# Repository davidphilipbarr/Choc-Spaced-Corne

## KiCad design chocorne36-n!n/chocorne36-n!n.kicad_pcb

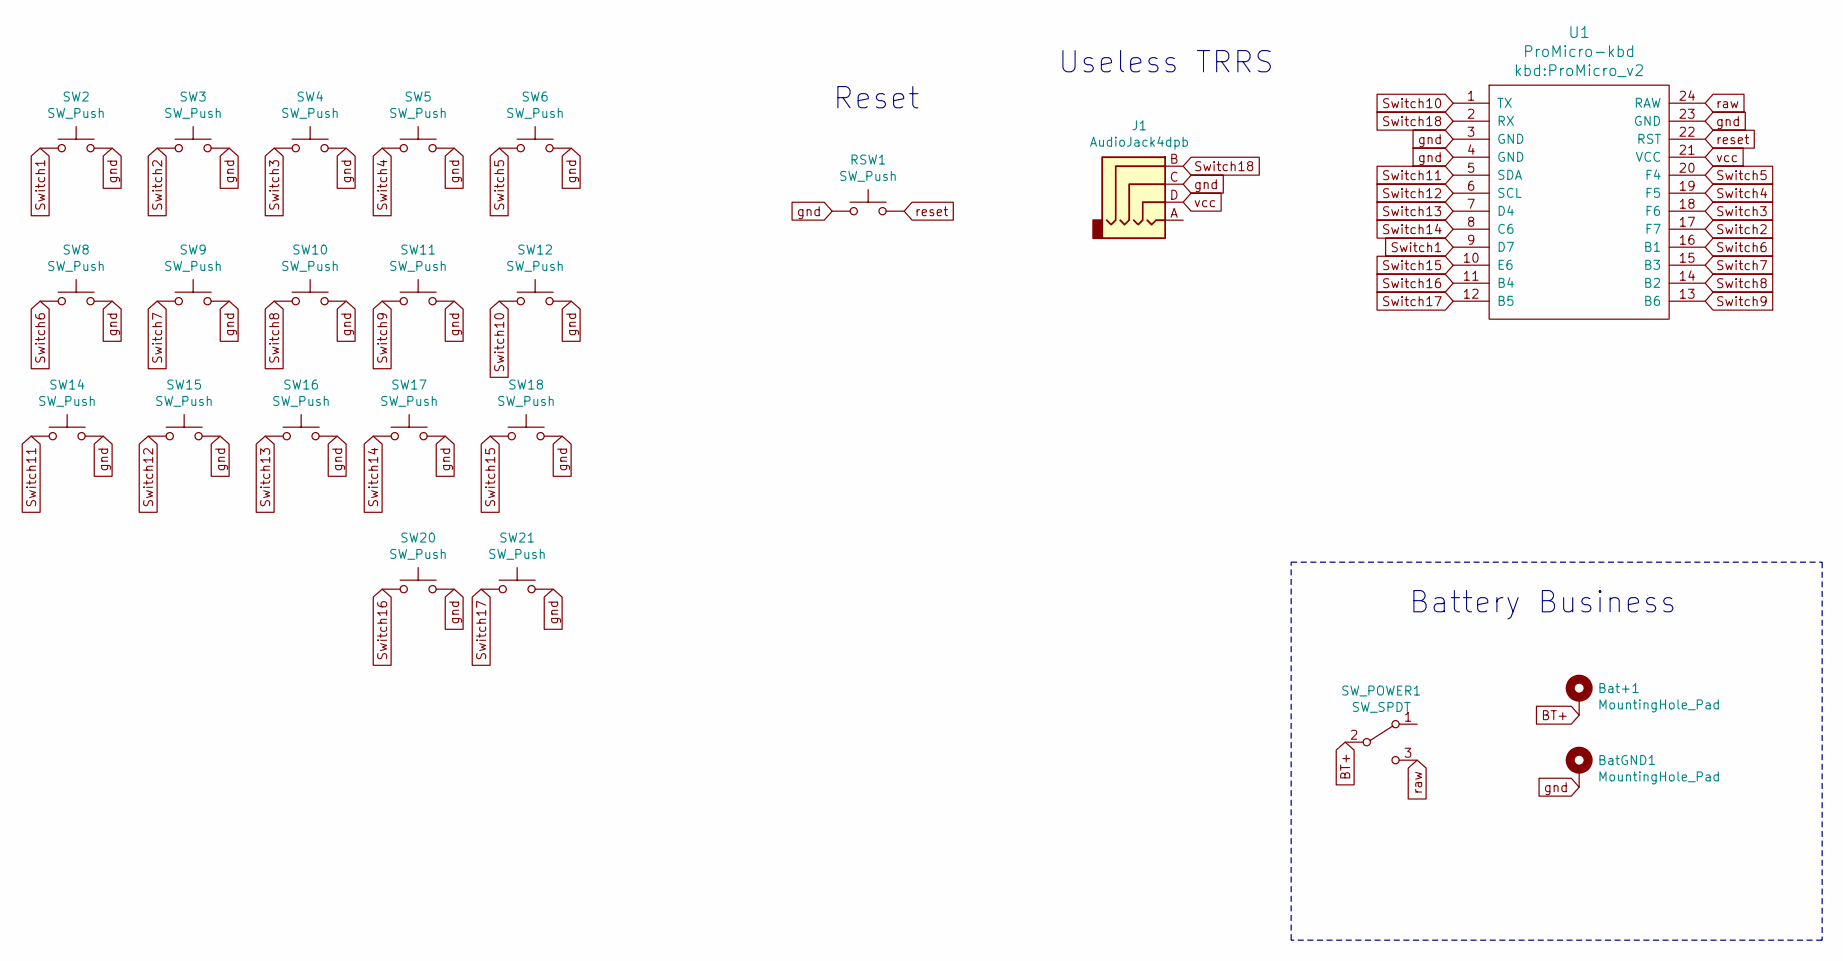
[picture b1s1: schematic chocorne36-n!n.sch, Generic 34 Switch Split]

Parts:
Bat+1: MountingHole_Pad; 1pin_conn
BatGND1: MountingHole_Pad; 1pin_conn
J1: AudioJack4dpb; MJ-4PP-9
RSW1: SW_Push; ResetSW
SW2, SW3, SW4, SW5, SW6, SW8, SW9, SW10, SW11, SW12, SW14, SW15, SW16, SW17, SW18, SW20, SW21: SW_Push; SW_PG1350_rev_DPB
SW_POWER1: SW_SPDT; SPDT_C128955
U1: ProMicro-kbd; ProMicro_v2

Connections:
BT+: Bat+1.1, SW_POWER1.2 (B)
Switch1: SW2.1, U1.9 (D7)
Switch2: SW3.1, U1.17 (F7)
Switch3: SW4.1, U1.18 (F6)
Switch4: SW5.1, U1.19 (F5)
Switch5: SW6.1, U1.20 (F4)
Switch6: SW8.1, U1.16 (B1)
Switch7: SW9.1, U1.15 (B3)
Switch8: SW10.1, U1.14 (B2)
Switch9: SW11.1, U1.13 (B6)
Switch10: SW12.1, U1.1 (TX)
Switch11: SW14.1, U1.5 (SDA)
Switch12: SW15.1, U1.6 (SCL)
Switch13: SW16.1, U1.7 (D4)
Switch14: SW17.1, U1.8 (C6)
Switch15: SW18.1, U1.10 (E6)
Switch16: SW20.1, U1.11 (B4)
Switch17: SW21.1, U1.12 (B5)
Switch18: J1.B, U1.2 (RX); also elsewhere on the board
gnd: BatGND1.1, J1.C, RSW1.1, SW2.2, SW3.2, SW4.2, SW5.2, SW6.2, SW8.2, SW9.2, SW10.2, SW11.2, SW12.2, SW14.2, SW15.2, SW16.2, SW17.2, SW18.2, SW20.2, SW21.2, U1.3 (GND), U1.4 (GND), U1.23 (GND); also elsewhere on the board
raw: SW_POWER1.3 (C), U1.24 (RAW)
reset: RSW1.2, U1.22 (RST)
vcc: J1.D, U1.21 (VCC)

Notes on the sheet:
Battery Business
Useless TRRS
Reset

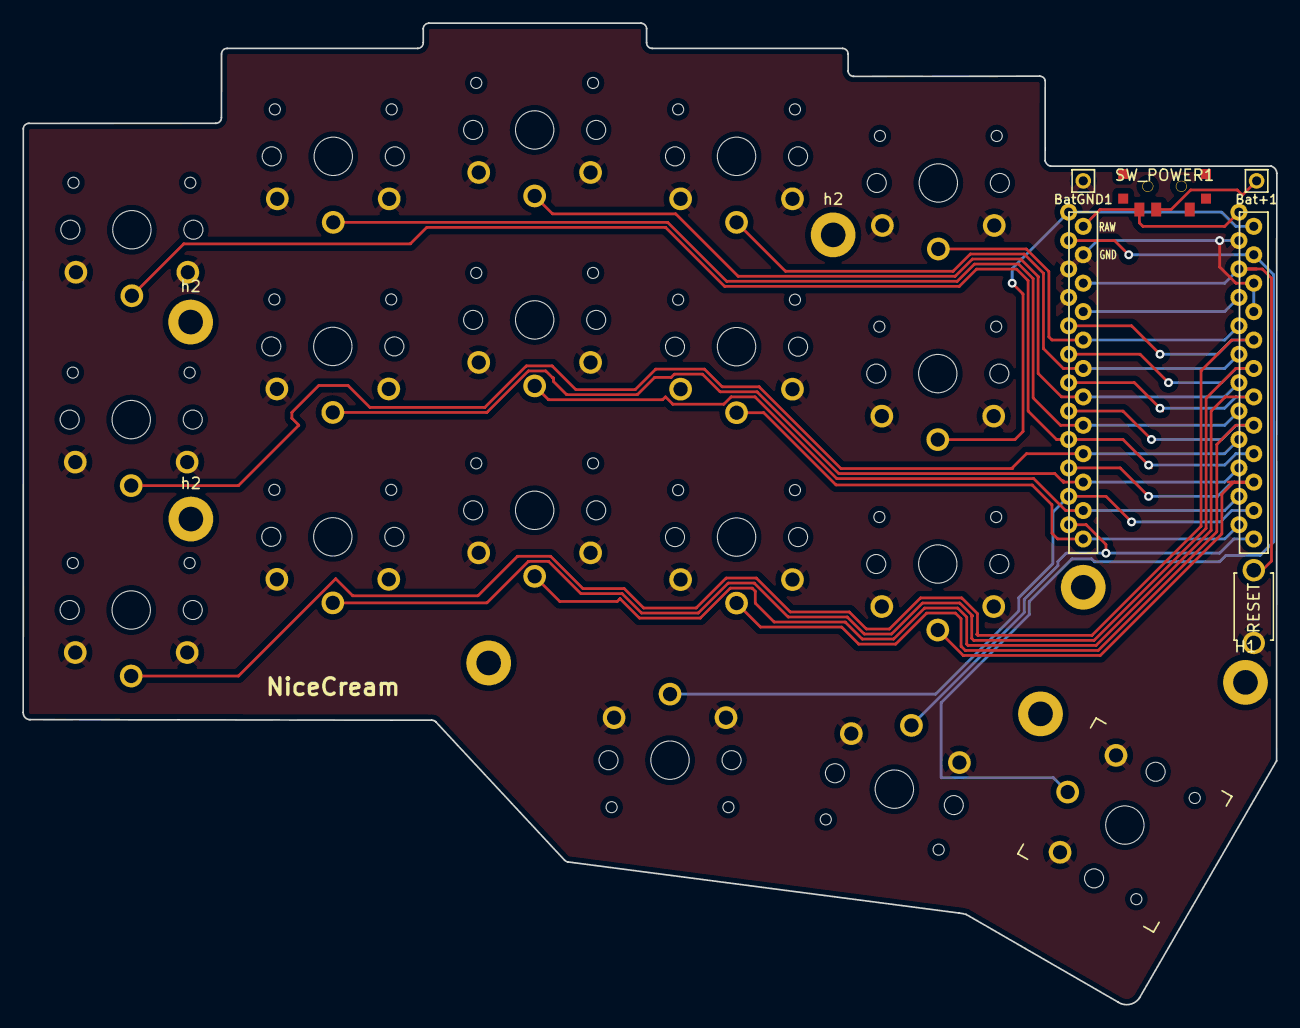
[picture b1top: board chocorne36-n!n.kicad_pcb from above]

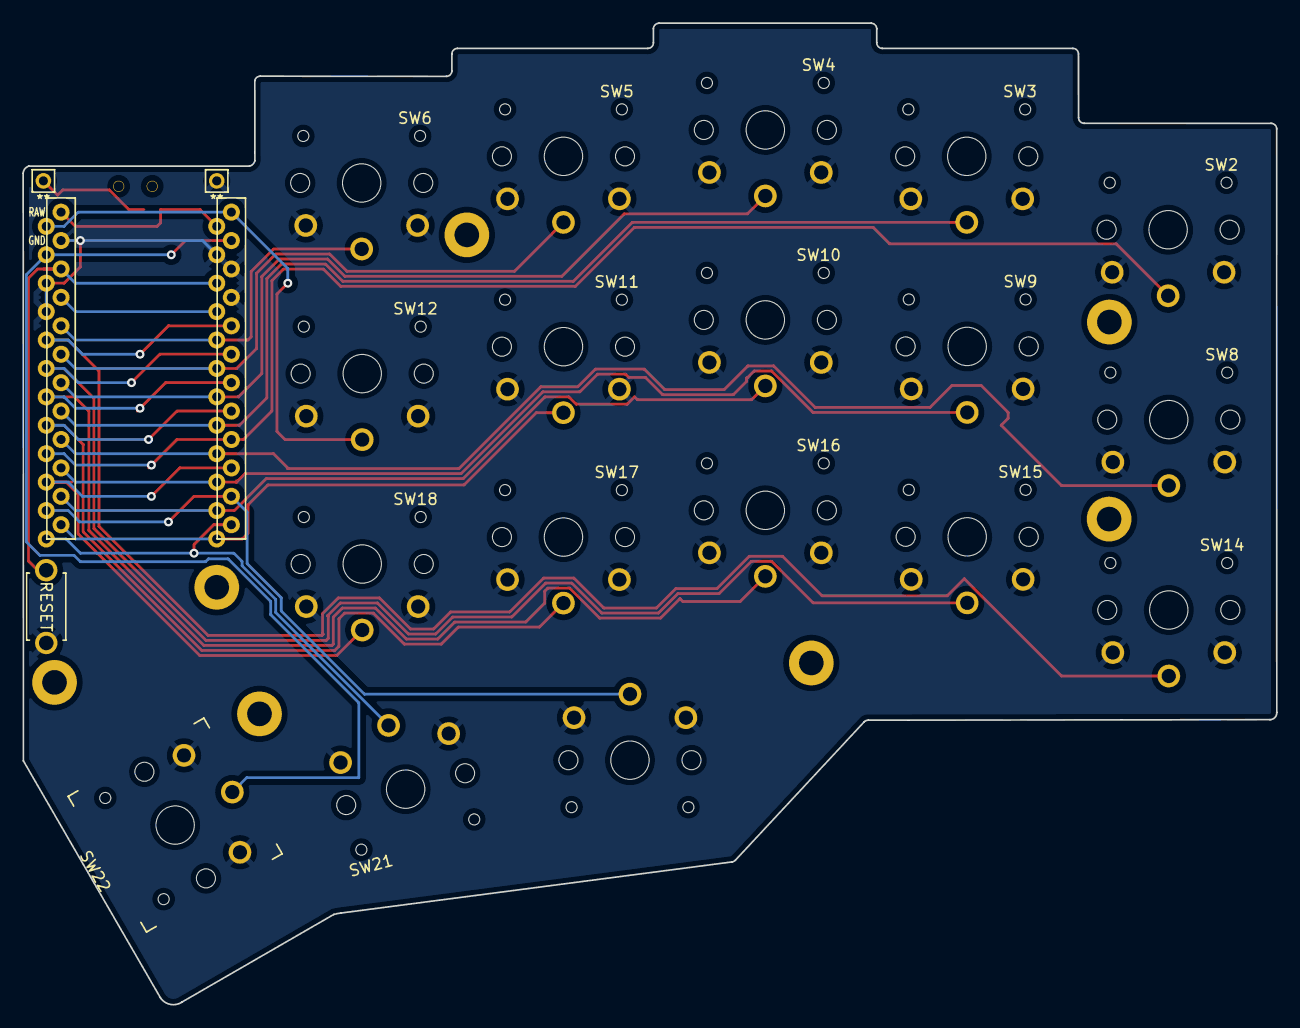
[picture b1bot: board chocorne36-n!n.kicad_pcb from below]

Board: 2 copper layers, 112.0 x 87.7 mm, 27 parts (2 on the bottom side), 22 nets.

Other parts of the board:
H1: h1; LEGO_HOLE
SW22: SW_Push; SW_PG1350_15_reversible_b2
h2, h2#2, h2#3: h2; LEGO_HOLE

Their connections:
Switch18: SW22.1; also elsewhere on the board
gnd: SW22.2; also elsewhere on the board

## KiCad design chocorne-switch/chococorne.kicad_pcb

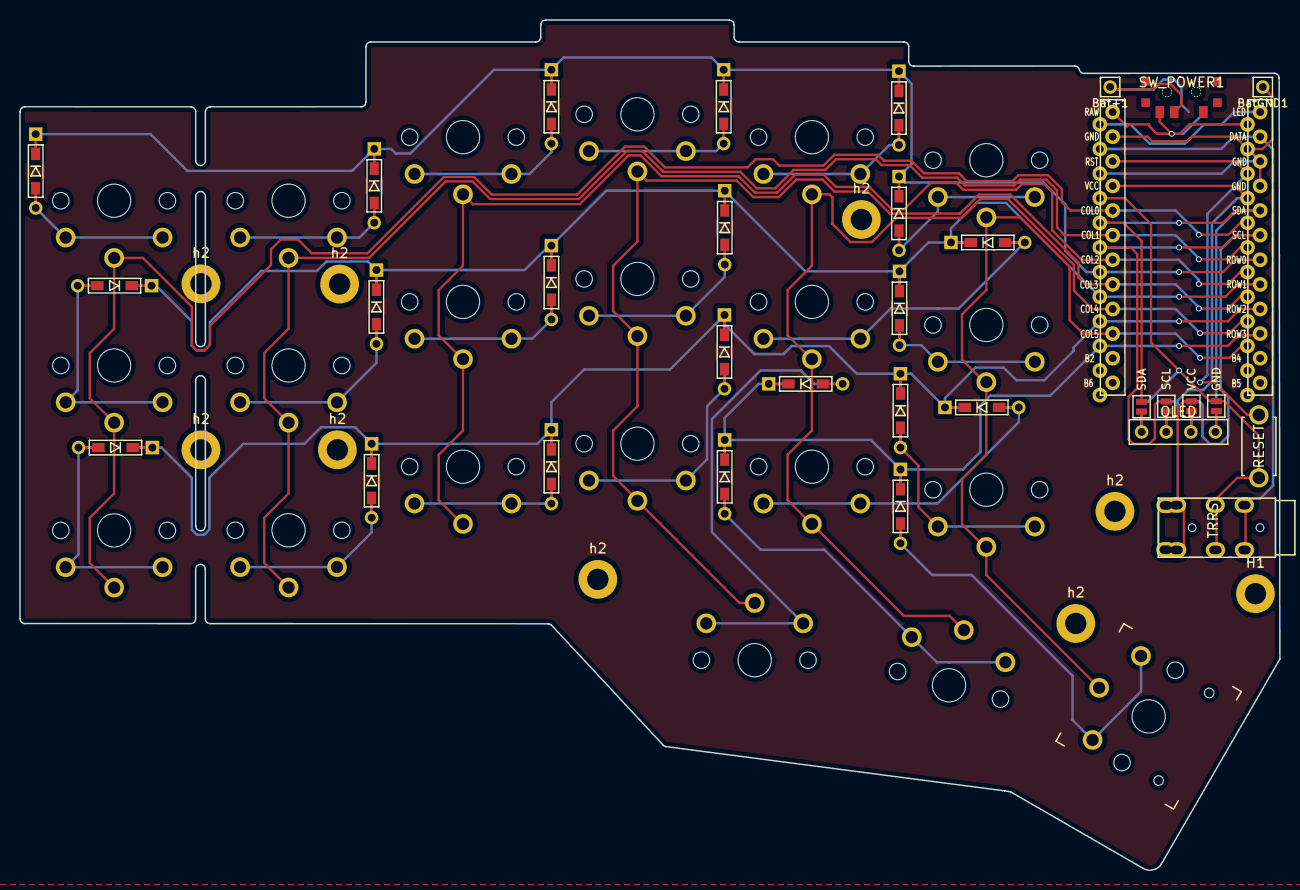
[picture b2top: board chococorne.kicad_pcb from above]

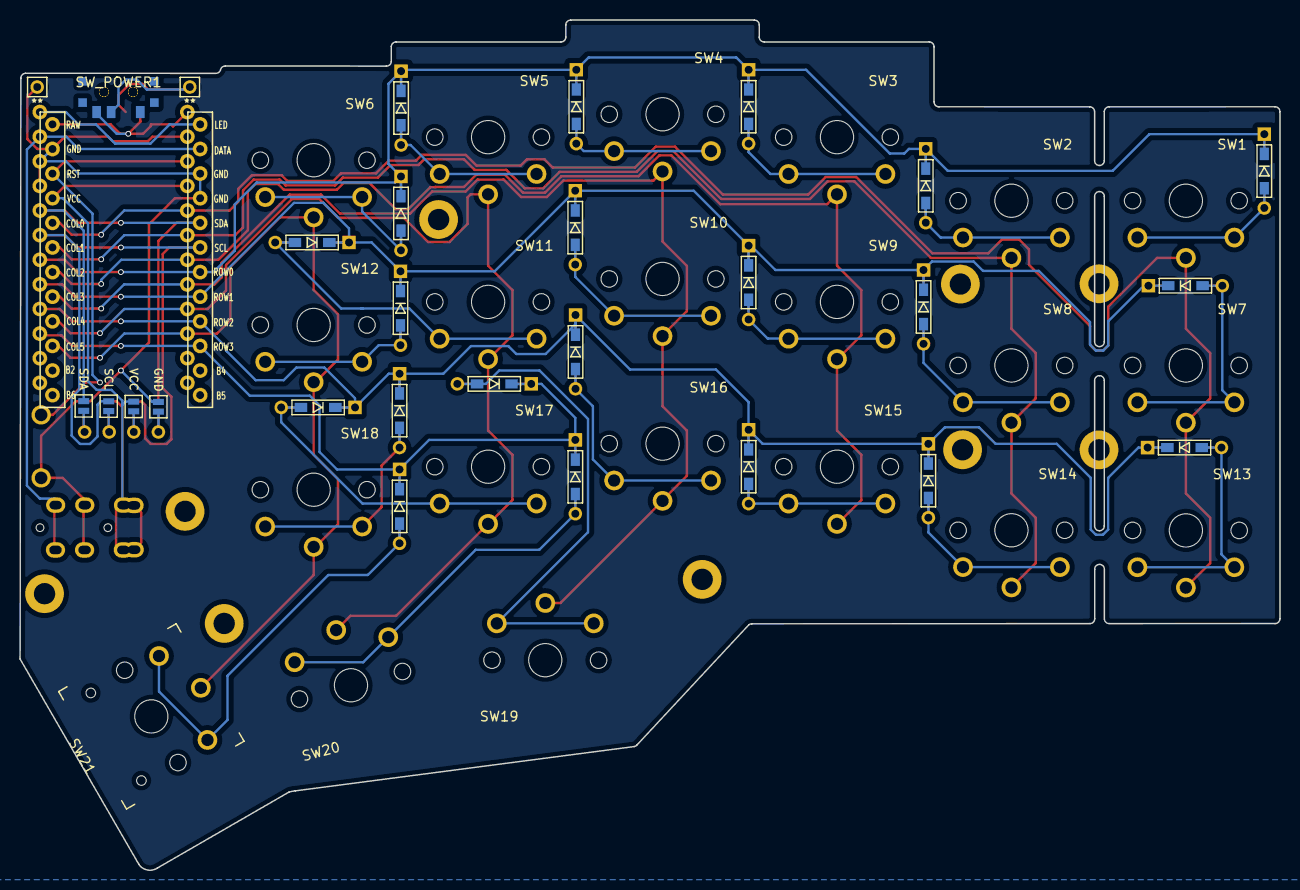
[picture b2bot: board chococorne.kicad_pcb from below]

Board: 2 copper layers, 130.0 x 87.7 mm, 67 parts (5 on the bottom side), 43 nets.

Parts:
Bat+1: MountingHole_Pad; 1pin_conn
BatGND1: MountingHole_Pad; 1pin_conn
D1, D2, D3, D4, D5, D6, D7, D8, D9, D10, D11, D12, D13, D14, D15, D16, D17, D18, D19, D20, D21: D; D3_TH_SMD
H1: h1; LEGO_HOLE
J1: MJ-4PP-9; TRRS-PJ-DPB2
J2: OLED; OLED_1side
JP6, JP61: SDA; Jumper
JP62, JP68: GND; Jumper
JP63, JP66: SCL; Jumper
JP64, JP65: VCC; Jumper
RSW1: SW_PUSH; ResetSW_1side
SW1, SW2, SW3, SW4, SW5, SW6, SW7, SW8, SW9, SW10, SW11, SW12, SW13, SW14, SW15, SW16, SW17, SW18, SW19, SW20: SW_PUSH; SW_PG1350_rev_DPB2.1
SW21: SW_PUSH; SW_PG1350_15_reversible_b2
SW_POWER1, SW_POWER1#2: SW_SPDT; SPDT_C128955
U1: ProMicro; ProMicro_v2
h2, h2#2, h2#3, h2#4, h2#5, h2#6, h2#7, h2#8: h2; LEGO_HOLE

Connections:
BT+: Bat+1.1, SW_POWER1.2 (B), SW_POWER1#2.2 (B)
GND: BatGND1.1, J1.R1, JP62.1, JP68.1, RSW1.1, U1.3 (GND), U1.4 (GND), U1.23 (GND)
unnamed: D1.2 (A), SW1.2
unnamed: D2.2 (A), SW2.2
unnamed: D3.2 (A), SW3.2
unnamed: D4.2 (A), SW4.2
unnamed: D5.2 (A), SW5.2
unnamed: D6.2 (A), SW6.2
unnamed: D7.2 (A), SW7.2
unnamed: D8.2 (A), SW8.2
unnamed: D9.2 (A), SW9.2
unnamed: D10.2 (A), SW10.2
unnamed: D11.2 (A), SW11.2
unnamed: D12.2 (A), SW12.2
unnamed: D13.2 (A), SW13.2
unnamed: D14.2 (A), SW14.2
unnamed: D15.2 (A), SW15.2
unnamed: D16.2 (A), SW16.2
unnamed: D17.2 (A), SW17.2
unnamed: D18.2 (A), SW18.2
unnamed: D19.2 (A), SW19.2
unnamed: D20.2 (A), SW20.2
unnamed: D21.2 (A), SW21.2
unnamed: J2.3, JP65.2, JP66.2
unnamed: J2.4, JP6.2, JP68.2
unnamed: J2.2, JP63.2, JP64.2
unnamed: J2.1, JP61.2, JP62.2
SCL: JP63.1, JP66.1, U1.6 (SCL)
SDA: JP6.1, JP61.1, U1.5 (SDA)
VCC: J1.S, J1.T, JP64.1, JP65.1, U1.21 (VCC)
col0: SW1.1, SW7.1, SW13.1, U1.20 (F4)
col1: SW2.1, SW8.1, SW14.1, U1.19 (F5)
col2: SW3.1, SW9.1, SW15.1, U1.18 (F6)
col3: SW4.1, SW10.1, SW16.1, SW19.1, U1.17 (F7)
col4: SW5.1, SW11.1, SW17.1, SW20.1, U1.16 (B1)
col5: SW6.1, SW12.1, SW18.1, SW21.1, U1.15 (B3)
data: J1.R2, U1.2 (RX)
raw: SW_POWER1.3 (C), SW_POWER1#2.3 (C), U1.24 (RAW)
reset: RSW1.2, U1.22 (RST)
row0: D1.1 (K), D2.1 (K), D3.1 (K), D4.1 (K), D5.1 (K), D6.1 (K), U1.7 (D4)
row1: D7.1 (K), D8.1 (K), D9.1 (K), D10.1 (K), D11.1 (K), D12.1 (K), U1.8 (C6)
row2: D13.1 (K), D14.1 (K), D15.1 (K), D16.1 (K), D17.1 (K), D18.1 (K), U1.9 (D7)
row3: D19.1 (K), D20.1 (K), D21.1 (K), U1.10 (E6)

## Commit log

2021-11-15 New home for chocorne
2022-02-07 add diodeless 36 key corne
2022-02-07 Add power switch to the chocorne (untested)
2022-02-07 Change the silks for the controller.
    Change the silks for the controller to avert future meltdowns about it.
2022-04-05 add new gerber
